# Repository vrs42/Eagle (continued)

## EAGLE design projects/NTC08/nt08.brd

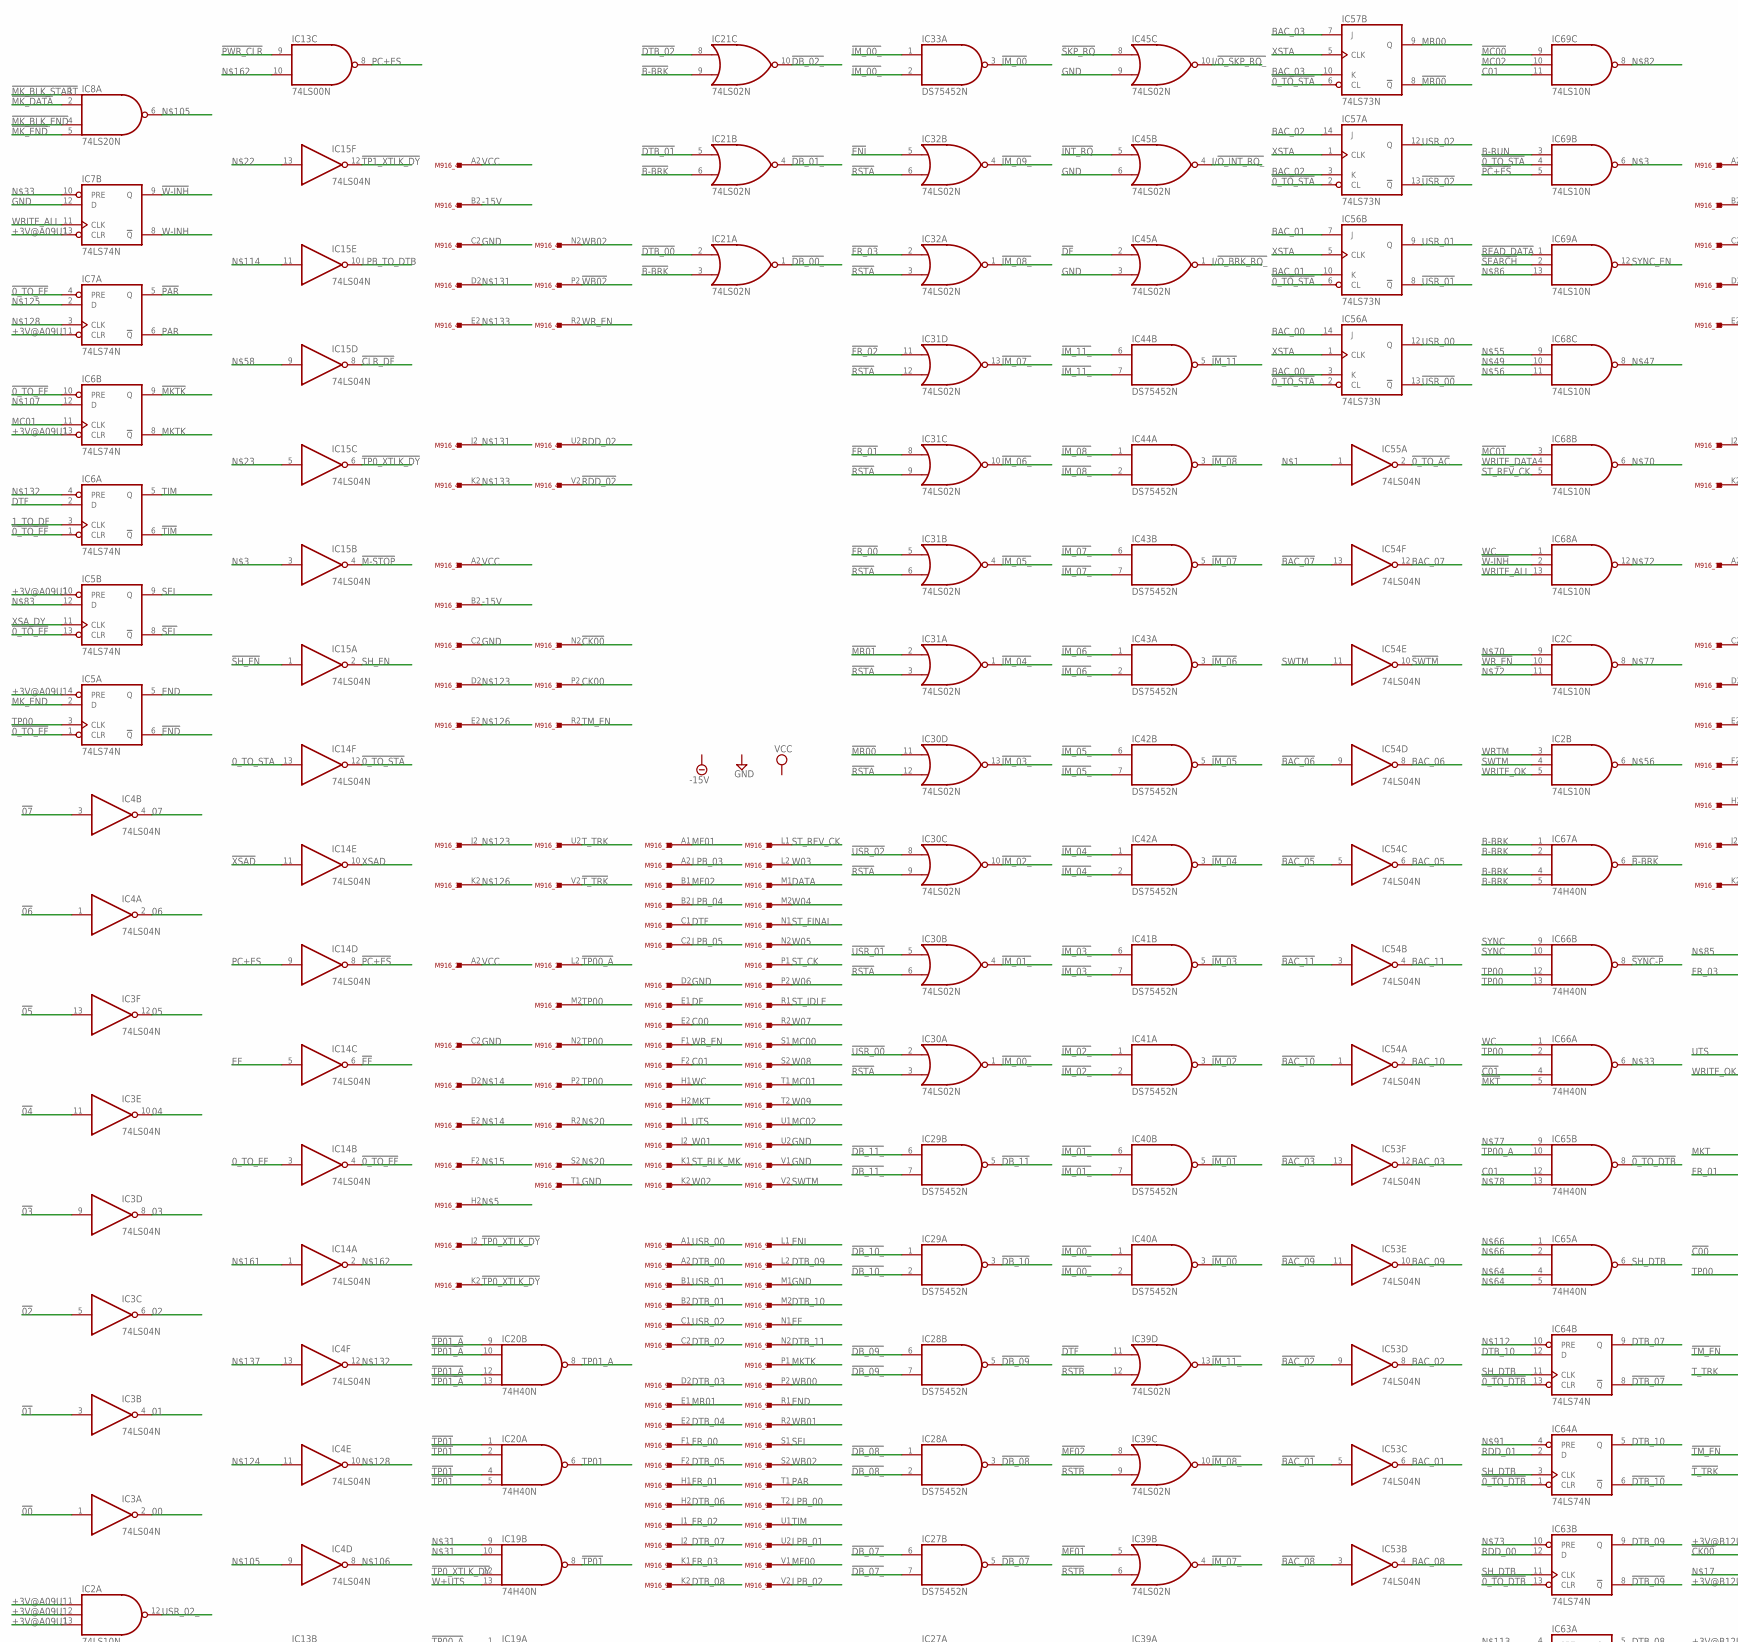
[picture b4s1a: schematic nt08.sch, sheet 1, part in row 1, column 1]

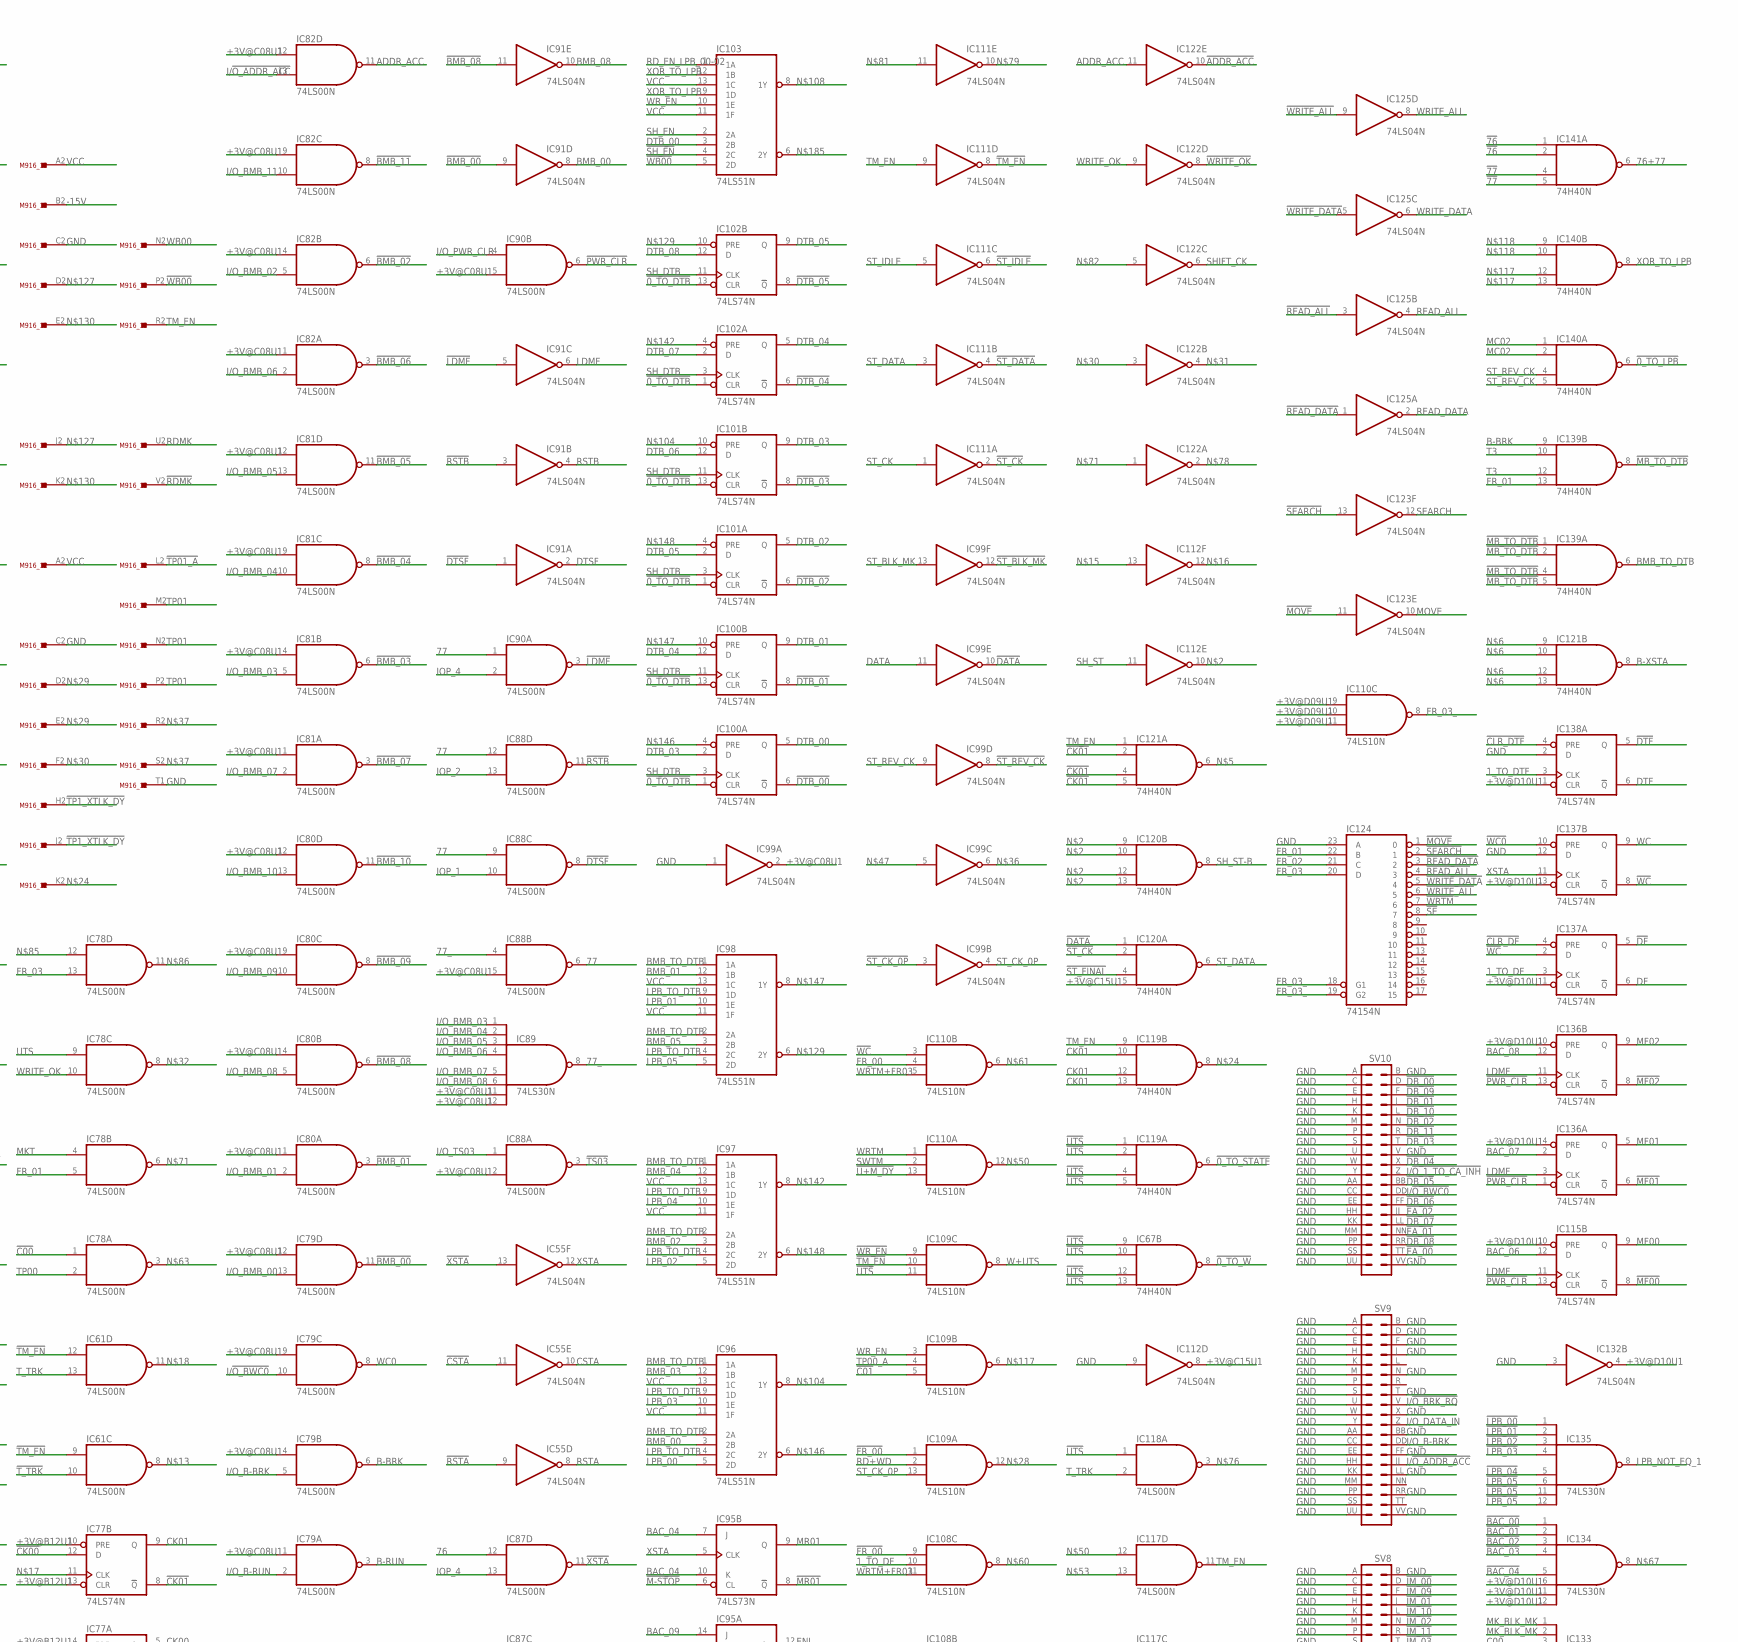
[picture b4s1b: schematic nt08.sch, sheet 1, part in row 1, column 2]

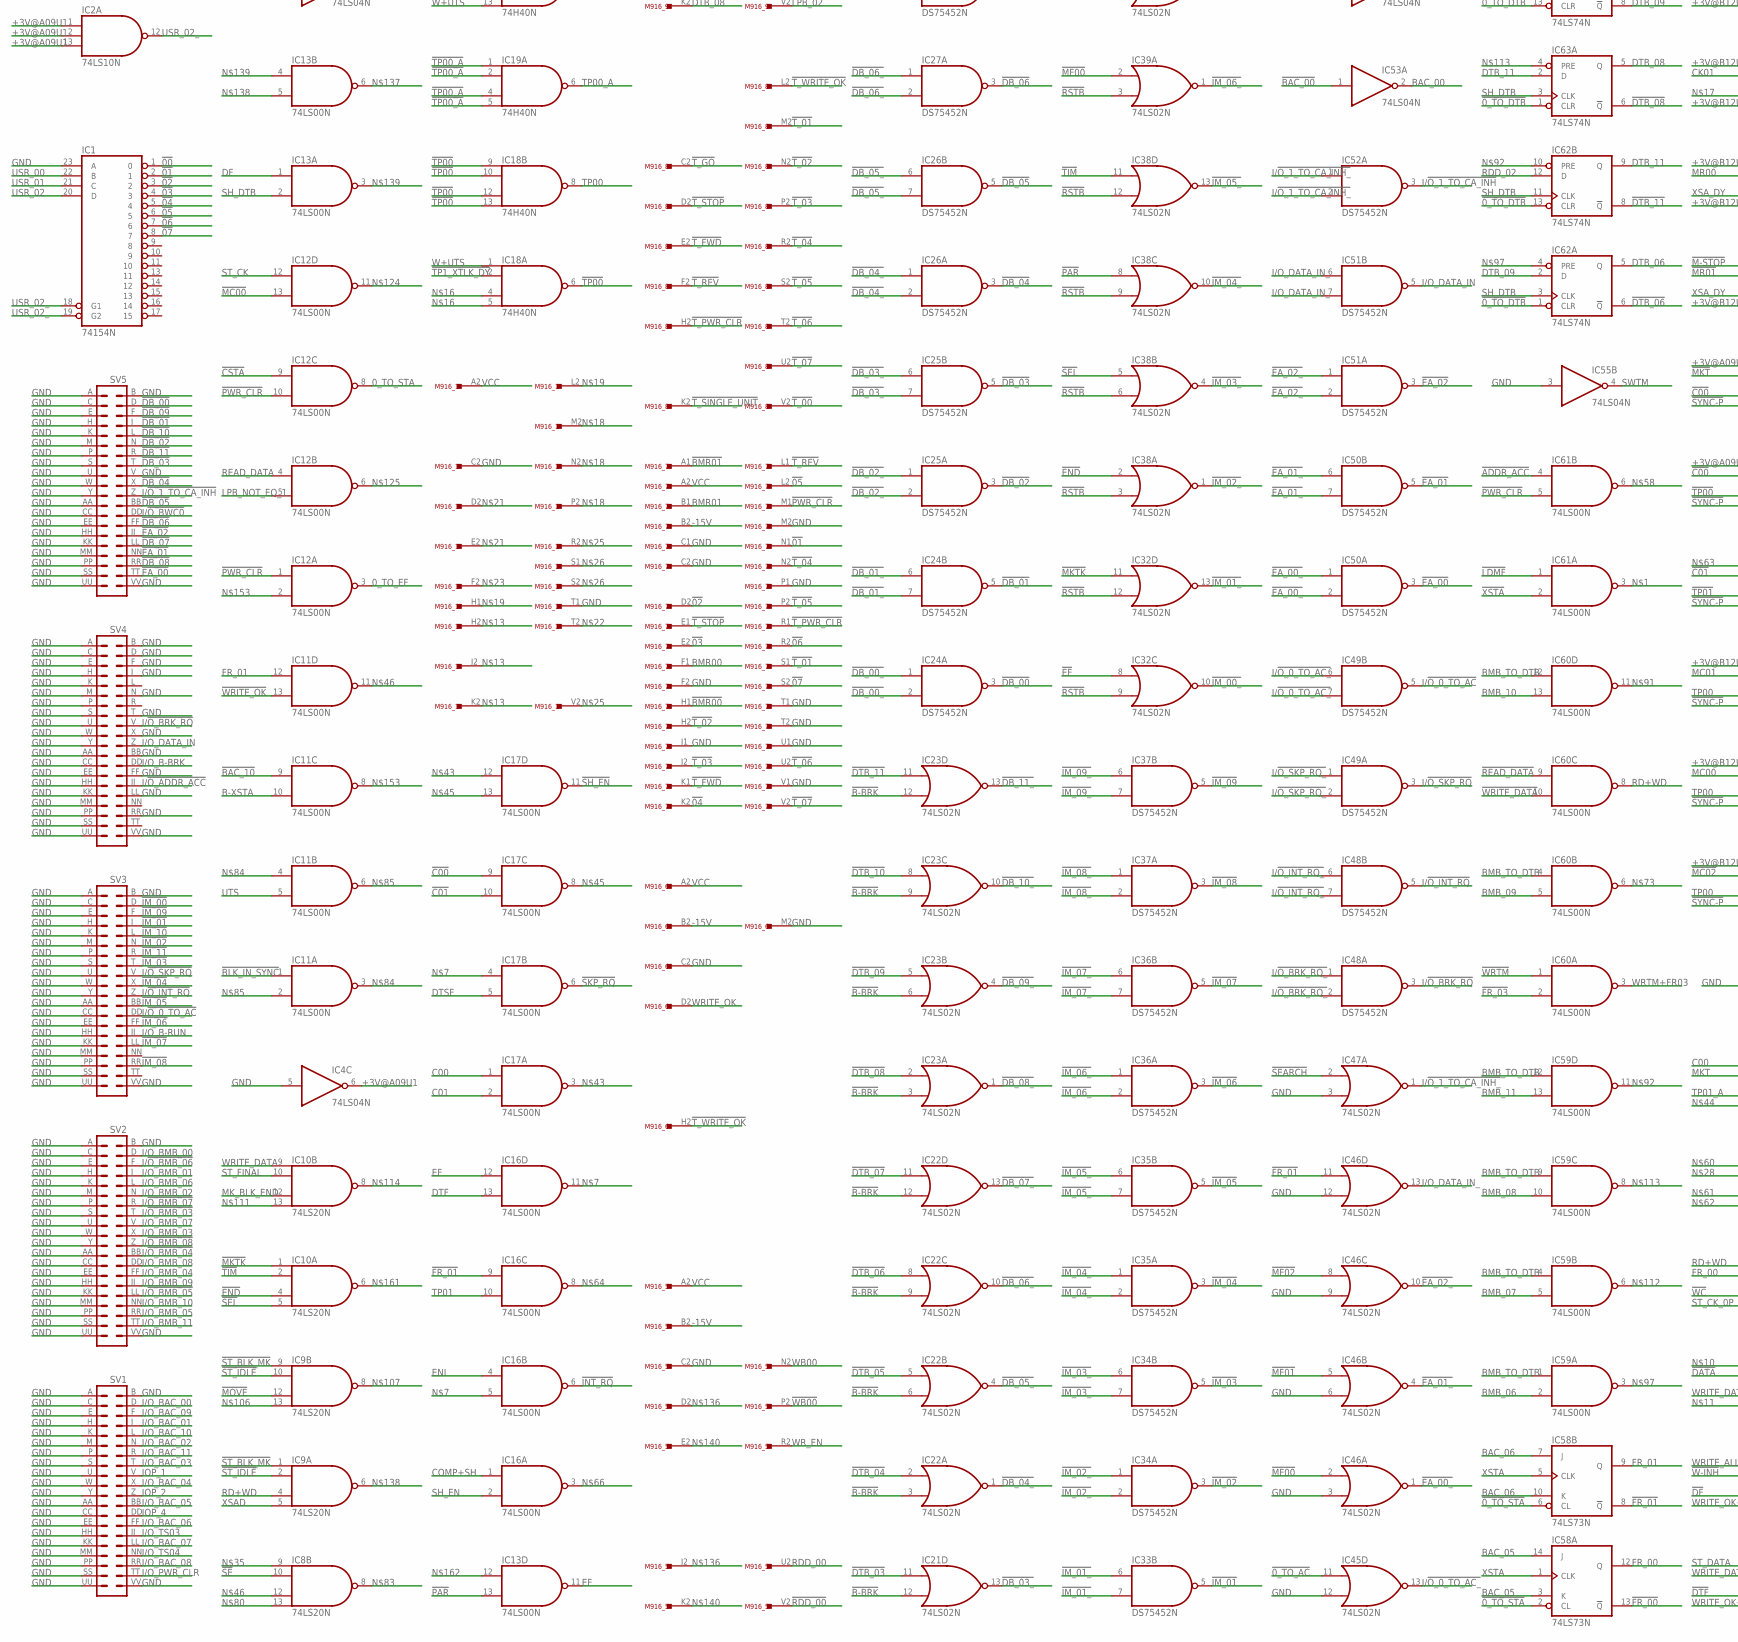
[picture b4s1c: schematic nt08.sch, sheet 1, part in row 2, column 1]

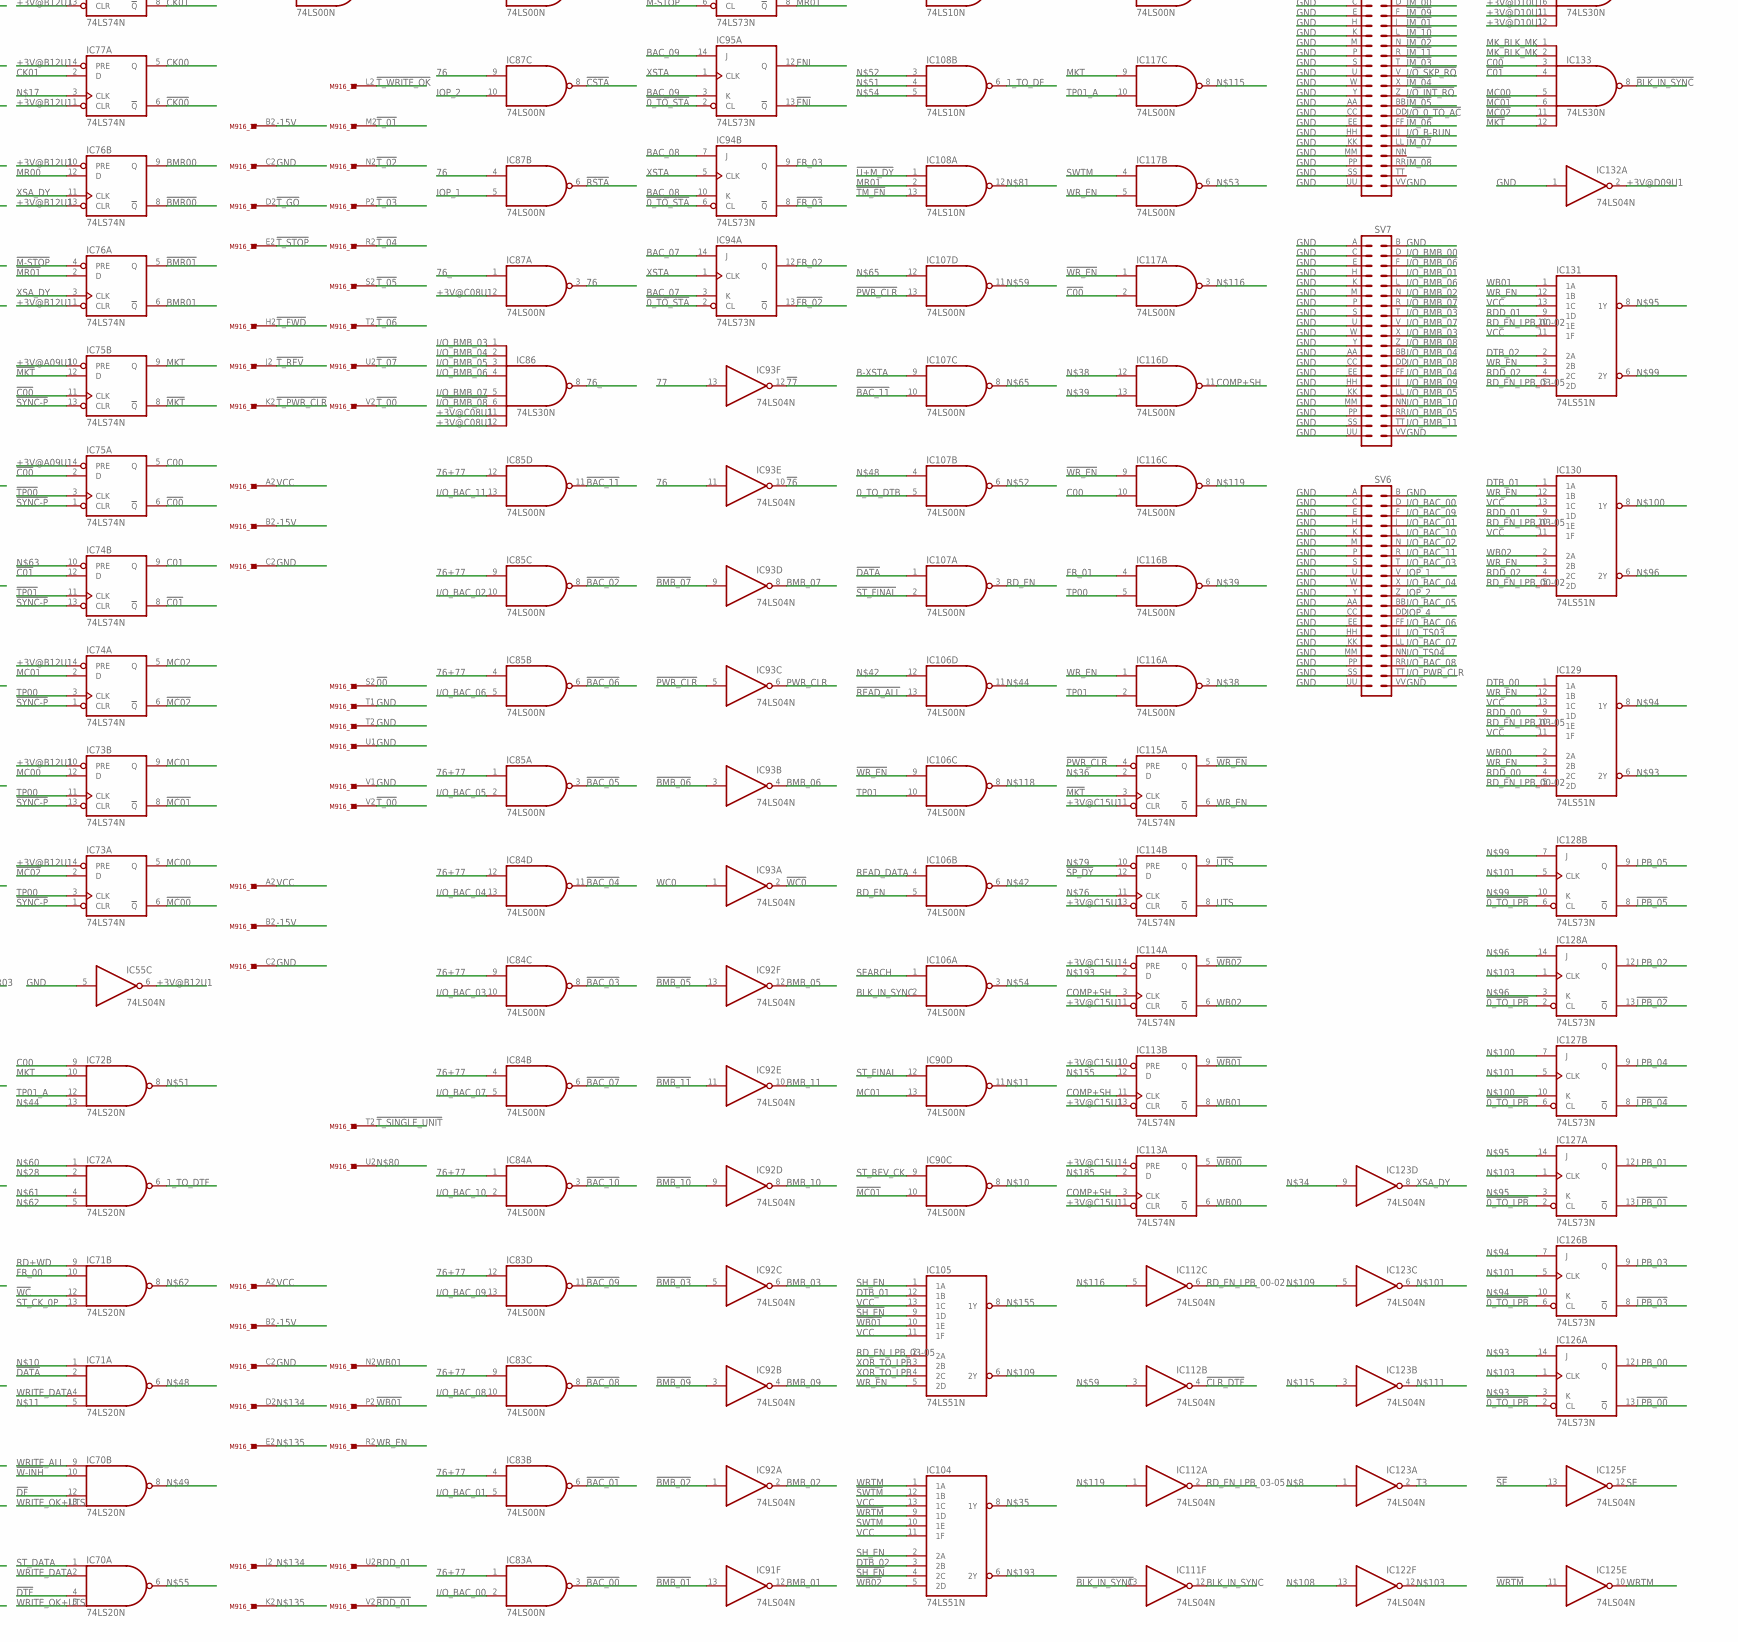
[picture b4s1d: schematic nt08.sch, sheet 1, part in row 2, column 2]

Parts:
IC1, IC124: 74154N; DIL24-6
IC2, IC68, IC69, IC108, IC109, IC110: 74LS10N; DIL14
IC3, IC4, IC14, IC15, IC53, IC54, IC55, IC91, IC92, IC93, IC99, IC111, IC112, IC122, IC123, IC125, IC132: 74LS04N; DIL14
IC5, IC6, IC7, IC62, IC63, IC64, IC73, IC74, IC75, IC76, IC77, IC100, IC101, IC102, IC113, IC114, IC115, IC136, IC137, IC138: 74LS74N; DIL14
IC8, IC9, IC10, IC70, IC71, IC72: 74LS20N; DIL14
IC11, IC12, IC13, IC16, IC17, IC59, IC60, IC61, IC78, IC79, IC80, IC81, IC82, IC83, IC84, IC85, IC87, IC88, IC90, IC106, IC107, IC116, IC117, IC118: 74LS00N; DIL14
IC18, IC19, IC20, IC65, IC66, IC67, IC119, IC120, IC121, IC139, IC140, IC141: 74H40N; DIL14
IC21, IC22, IC23, IC30, IC31, IC32, IC38, IC39, IC45, IC46, IC47: 74LS02N; DIL14
IC24, IC25, IC26, IC27, IC28, IC29, IC33, IC34, IC35, IC36, IC37, IC40, IC41, IC42, IC43, IC44, IC48, IC49, IC50, IC51, IC52: DS75452N; DIL08
IC56, IC57, IC58, IC94, IC95, IC126, IC127, IC128: 74LS73N; DIL14
IC86, IC89, IC133, IC134, IC135: 74LS30N; DIL14
IC96, IC97, IC98, IC103, IC104, IC105, IC129, IC130, IC131: 74LS51N; DIL14
M916_1, M916_4: M302; H807
M916_2, M916_12: M602; H807
M916_3, M916_5, M916_6, M916_13, M916_14: G888; H807
M916_7, M916_16: M633; H807
M916_8: W023; H807
M916_9, M916_10: M916; H807
M916_15: G879; H807
M916_17: W005; H807
SV1, SV2, SV3, SV4, SV5, SV6, SV7, SV8, SV9, SV10: DEC40PINV

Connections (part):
00: IC3.2 (O)
0_TO_DTB: IC107.5 (I1)
0_TO_EF: IC12.3 (O), IC14.3 (I)
0_TO_STA: IC12.8 (O), IC14.13 (I)
01: IC3.4 (O)
1_TO_DF: IC6.3 (CLK), IC108.6 (O), IC108.10 (I1), IC137.3 (CLK)
1_TO_DTF: IC72.6 (O), IC138.3 (CLK)
02: IC3.6 (O)
03: IC3.8 (O)
04: IC3.10 (O)
05: IC3.12 (O)
06: IC4.2 (O)
07: IC4.4 (O)
76: IC87.3 (O), IC87.4 (I0), IC87.9 (I0), IC87.12 (I0), IC93.11 (I)
76+77: IC83.1 (I0), IC83.4 (I0), IC83.9 (I0), IC83.12 (I0), IC84.1 (I0), IC84.4 (I0), IC84.9 (I0), IC84.12 (I0), IC85.1 (I0), IC85.4 (I0), IC85.9 (I0), IC85.12 (I0), IC141.6 (O)
76_: IC86.8 (O), IC87.1 (I0)
77: IC88.6 (O), IC88.9 (I0), IC88.12 (I0), IC90.1 (I0), IC93.13 (I)
77_: IC88.4 (I0), IC89.8 (O)
!00: IC1.1 (0), IC3.1 (I), M916_16.S2
!0_TO_AC: IC45.11 (I0), IC55.2 (O)
!0_TO_DTB: IC62.1 (CLR), IC62.13 (CLR), IC63.1 (CLR), IC63.13 (CLR), IC64.1 (CLR), IC64.13 (CLR), IC65.8 (O), IC100.1 (CLR), IC100.13 (CLR), IC101.1 (CLR), IC101.13 (CLR), IC102.1 (CLR), IC102.13 (CLR)
!0_TO_EF: IC5.1 (CLR), IC5.13 (CLR), IC6.1 (CLR), IC6.10 (PRE), IC7.4 (PRE), IC14.4 (O)
!0_TO_LPB: IC126.2 (CL), IC126.6 (CL), IC127.2 (CL), IC127.6 (CL), IC128.2 (CL), IC128.6 (CL), IC140.6 (O)
!0_TO_STA: IC14.12 (O), IC56.2 (CL), IC56.6 (CL), IC57.2 (CL), IC57.6 (CL), IC58.2 (CL), IC58.6 (CL), IC69.4 (I1), IC94.2 (CL), IC94.6 (CL), IC95.2 (CL)
!0_TO_STATE: IC119.6 (O)
!0_TO_W: IC67.8 (O)
!01: IC1.2 (1), IC3.3 (I), M916_7.N1
!02: IC1.3 (2), IC3.5 (I), M916_7.D2
!03: IC1.4 (3), IC3.9 (I), M916_7.E2
!04: IC1.5 (4), IC3.11 (I), M916_7.K2
!05: IC1.6 (5), IC3.13 (I), M916_7.L2
!06: IC1.7 (6), IC4.1 (I), M916_7.R2
!07: IC1.8 (7), IC4.3 (I), M916_7.S2
!76: IC93.10 (O), IC141.1 (I0), IC141.2 (I1)
!77: IC93.12 (O), IC141.4 (I2), IC141.5 (I3)
!ADDR_ACC: IC61.4 (I0), IC122.10 (O)
!B-BRK: IC21.3 (I1), IC21.6 (I1), IC21.9 (I1), IC21.12 (I1), IC22.3 (I1), IC22.6 (I1), IC22.9 (I1), IC22.12 (I1), IC23.3 (I1), IC23.6 (I1), IC23.9 (I1), IC23.12 (I1), IC67.6 (O)
!BAC_00: IC53.1 (I), IC83.3 (O), IC134.1 (I0)
!BAC_01: IC53.5 (I), IC83.6 (O), IC134.2 (I1)
!BAC_02: IC53.9 (I), IC85.8 (O), IC134.3 (I2)
!BAC_03: IC53.13 (I), IC84.8 (O), IC134.4 (I3)
!BAC_04: IC84.11 (O), IC134.5 (I4)
!BAC_05: IC54.5 (I), IC85.3 (O)
!BAC_06: IC54.9 (I), IC85.6 (O)
!BAC_07: IC54.13 (I), IC84.6 (O)
!BAC_08: IC53.3 (I), IC83.8 (O)
!BAC_09: IC53.11 (I), IC83.11 (O)
!BAC_10: IC11.9 (I0), IC54.1 (I), IC84.3 (O)
!BAC_11: IC54.3 (I), IC85.11 (O), IC107.10 (I1)
!BLK_IN_SYNC: IC11.1 (I0), IC111.13 (I), IC133.8 (O)
!BMB_00: IC79.11 (O), IC91.9 (I)
!BMB_01: IC80.3 (O), IC91.13 (I)
!BMB_02: IC82.6 (O), IC92.1 (I)
!BMB_03: IC81.6 (O), IC92.5 (I)
!BMB_04: IC81.8 (O)
!BMB_05: IC81.11 (O), IC92.13 (I)
!BMB_06: IC82.3 (O), IC93.3 (I)
!BMB_07: IC81.3 (O), IC93.9 (I)
!BMB_08: IC80.6 (O), IC91.11 (I)
!BMB_09: IC80.8 (O), IC92.3 (I)
!BMB_10: IC80.11 (O), IC92.9 (I)
!BMB_11: IC82.8 (O), IC92.11 (I)
!BMR00: IC76.8 (!Q), M916_7.H1
!BMR01: IC76.5 (Q), M916_7.A1
!C00: IC17.9 (I0), IC75.2 (D), IC75.6 (!Q), IC75.11 (CLK), IC78.1 (I0), IC117.2 (I1)
!C01: IC17.10 (I1), IC66.4 (I2), IC74.8 (!Q), IC74.12 (D), IC109.5 (I2), IC133.4 (I3)
!CK00: IC77.6 (!Q), IC77.12 (D), M916_3.N2
!CK01: IC77.8 (!Q), IC121.2 (I1), IC121.4 (I2), IC121.5 (I3)
!CLR_DF: IC15.8 (O), IC137.4 (PRE)
!CLR_DTF: IC112.4 (O), IC138.4 (PRE)
!CSTA: IC12.9 (I0), IC55.11 (I), IC87.8 (O)
!DATA: IC71.2 (I1), IC99.10 (O), IC107.1 (I0), IC120.1 (I0)
!DB_00: IC24.3 (O), SV5.D (4), SV10.D (4)
!DB_00_: IC21.1 (O), IC24.1 (I0), IC24.2 (I1)
!DB_01: IC24.5 (O), SV5.J (8), SV10.J (8)
!DB_01_: IC21.4 (O), IC24.6 (I0), IC24.7 (I1)
!DB_02: IC25.3 (O), SV5.N (12), SV10.N (12)
!DB_02_: IC21.10 (O), IC25.1 (I0), IC25.2 (I1)
!DB_03: IC25.5 (O), SV5.T (16), SV10.T (16)
!DB_03_: IC21.13 (O), IC25.6 (I0), IC25.7 (I1)
!DB_04: IC26.3 (O), SV5.X (20), SV10.X (20)
!DB_04_: IC22.1 (O), IC26.1 (I0), IC26.2 (I1)
!DB_05: IC26.5 (O), SV5.BB (24), SV10.BB (24)
!DB_05_: IC22.4 (O), IC26.6 (I0), IC26.7 (I1)
!DB_06: IC27.3 (O), SV5.FF (28), SV10.FF (28)
!DB_06_: IC22.10 (O), IC27.1 (I0), IC27.2 (I1)
!DB_07: IC27.5 (O), SV5.LL (32), SV10.LL (32)
!DB_07_: IC22.13 (O), IC27.6 (I0), IC27.7 (I1)
!DB_08: IC28.3 (O), SV5.RR (36), SV10.RR (36)
!DB_08_: IC23.1 (O), IC28.1 (I0), IC28.2 (I1)
!DB_09: IC28.5 (O), SV5.F (6), SV10.F (6)
!DB_09_: IC23.4 (O), IC28.6 (I0), IC28.7 (I1)
!DB_10: IC29.3 (O), SV5.L (10), SV10.L (10)
!DB_10_: IC23.10 (O), IC29.1 (I0), IC29.2 (I1)
!DB_11: IC29.5 (O), SV5.R (14), SV10.R (14)
!DB_11_: IC23.13 (O), IC29.6 (I0), IC29.7 (I1)
!DF: IC45.2 (I0), IC70.12 (I2), IC137.5 (Q)
!DTB_00: IC21.2 (I0), IC100.6 (!Q)
!DTB_01: IC21.5 (I0), IC100.8 (!Q)
!DTB_02: IC21.8 (I0), IC101.6 (!Q)
!DTB_03: IC21.11 (I0), IC101.8 (!Q)
!DTB_04: IC22.2 (I0), IC102.6 (!Q)
!DTB_05: IC22.5 (I0), IC102.8 (!Q)
!DTB_06: IC22.8 (I0), IC62.6 (!Q)
!DTB_07: IC22.11 (I0), IC64.8 (!Q)
!DTB_08: IC23.2 (I0), IC63.6 (!Q)
!DTB_09: IC23.5 (I0), IC63.8 (!Q)
!DTB_10: IC23.8 (I0), IC64.6 (!Q)
!DTB_11: IC23.11 (I0), IC62.8 (!Q)
!DTF: IC39.11 (I0), IC70.4 (I2), IC138.5 (Q)
!DTSF: IC88.8 (O), IC91.1 (I)
!EA_00: IC50.3 (O), SV5.TT (38), SV10.TT (38)
!EA_00_: IC46.1 (O), IC50.1 (I0), IC50.2 (I1)
!EA_01: IC50.5 (O), SV5.NN (34), SV10.NN (34)
!EA_01_: IC46.4 (O), IC50.6 (I0), IC50.7 (I1)
!EA_02: IC51.3 (O), SV5.JJ (30), SV10.JJ (30)
!EA_02_: IC46.10 (O), IC51.1 (I0), IC51.2 (I1)
!EF: IC14.6 (O), IC32.8 (I0)
!END: IC5.6 (!Q), IC10.4 (I2), IC38.2 (I0)
!ENI: IC32.5 (I0), IC95.13 (!Q)
!FR_00: IC31.5 (I0), IC58.13 (!Q), IC108.9 (I0), IC109.1 (I0)
!FR_01: IC16.9 (I0), IC31.8 (I0), IC46.11 (I0), IC58.8 (!Q)
!FR_02: IC31.11 (I0), IC94.13 (!Q)
!FR_03: IC32.2 (I0), IC60.2 (I1), IC94.8 (!Q)
!IM_00: IC33.3 (O), IC40.3 (O), SV3.D (4), SV8.D (4)
!IM_00_: IC30.1 (O), IC32.10 (O), IC33.1 (I0), IC33.2 (I1), IC40.1 (I0), IC40.2 (I1)
!IM_01: IC33.5 (O), IC40.5 (O), SV3.J (8), SV8.J (8)
!IM_01_: IC30.4 (O), IC32.13 (O), IC33.6 (I0), IC33.7 (I1), IC40.6 (I0), IC40.7 (I1)
!IM_02: IC34.3 (O), IC41.3 (O), SV3.N (12), SV8.N (12)
!IM_02_: IC30.10 (O), IC34.1 (I0), IC34.2 (I1), IC38.1 (O), IC41.1 (I0), IC41.2 (I1)
!IM_03: IC34.5 (O), IC41.5 (O), SV3.T (16), SV8.T (16)
!IM_03_: IC30.13 (O), IC34.6 (I0), IC34.7 (I1), IC38.4 (O), IC41.6 (I0), IC41.7 (I1)
!IM_04: IC35.3 (O), IC42.3 (O), SV3.X (20), SV8.X (20)
!IM_04_: IC31.1 (O), IC35.1 (I0), IC35.2 (I1), IC38.10 (O), IC42.1 (I0), IC42.2 (I1)
!IM_05: IC35.5 (O), IC42.5 (O), SV3.BB (24), SV8.BB (24)
!IM_05_: IC31.4 (O), IC35.6 (I0), IC35.7 (I1), IC38.13 (O), IC42.6 (I0), IC42.7 (I1)
!IM_06: IC36.3 (O), IC43.3 (O), SV3.FF (28), SV8.FF (28)
!IM_06_: IC31.10 (O), IC36.1 (I0), IC36.2 (I1), IC39.1 (O), IC43.1 (I0), IC43.2 (I1)
!IM_07: IC36.5 (O), IC43.5 (O), SV3.LL (32), SV8.LL (32)
!IM_07_: IC31.13 (O), IC36.6 (I0), IC36.7 (I1), IC39.4 (O), IC43.6 (I0), IC43.7 (I1)
!IM_08: IC37.3 (O), IC44.3 (O), SV3.RR (36), SV8.RR (36)
!IM_08_: IC32.1 (O), IC37.1 (I0), IC37.2 (I1), IC39.10 (O), IC44.1 (I0), IC44.2 (I1)
!IM_09: IC37.5 (O), SV3.F (6), SV8.F (6)
!IM_09_: IC32.4 (O), IC37.6 (I0), IC37.7 (I1)
!IM_10: SV3.L (10), SV8.L (10)
!IM_11: IC44.5 (O), SV3.R (14), SV8.R (14)
!IM_11_: IC39.13 (O), IC44.6 (I0), IC44.7 (I1)
!INT_RQ: IC16.6 (O), IC45.5 (I0)
!LDMF: IC61.1 (I0), IC90.3 (O), IC91.5 (I)
!LPB_00: IC126.13 (!Q), IC135.1 (I0)
!LPB_01: IC127.13 (!Q), IC135.2 (I1)
!LPB_02: IC128.13 (!Q), IC135.3 (I2)
!LPB_03: IC126.8 (!Q), IC135.4 (I3)
!LPB_04: IC127.8 (!Q), IC135.5 (I4)
!LPB_05: IC128.8 (!Q), IC135.6 (I5), IC135.11 (I6), IC135.12 (I7)
!M-STOP: IC15.4 (O), IC76.4 (PRE), IC95.6 (CL); also elsewhere on the board
!MB_TO_DTB: IC139.1 (I0), IC139.2 (I1), IC139.4 (I2), IC139.5 (I3), IC139.8 (O)
!MC00: IC12.13 (I1), IC69.9 (I0), IC73.6 (!Q)
!MC01: IC68.3 (I0), IC73.8 (!Q), IC90.10 (I1), IC133.6 (I5)
!MC02: IC73.2 (D), IC74.6 (!Q), IC133.11 (I6)
!MF00: IC39.2 (I0), IC46.2 (I0), IC115.8 (!Q)
!MF01: IC39.5 (I0), IC46.5 (I0), IC136.6 (!Q)
!MF02: IC39.8 (I0), IC46.8 (I0), IC136.8 (!Q)
!MKT: IC66.5 (I3), IC75.8 (!Q), IC75.12 (D), IC115.3 (CLK), IC133.12 (I7)
!MKTK: IC6.9 (Q), IC10.1 (I0), IC32.11 (I0)
!MK_BLK_END: IC8.4 (I2)
!MK_BLK_START: IC8.1 (I0)
!MK_DATA: IC8.2 (I1)
!MK_END: IC8.5 (I3)
!MOVE: IC9.12 (I2), IC123.11 (I), IC124.1 (0)
!MR00: IC30.11 (I0), IC57.8 (!Q)
!MR01: IC31.2 (I0), IC76.2 (D), IC95.8 (!Q)
!PAR: IC7.5 (Q), IC13.13 (I1), IC38.8 (I0)
!PC+ES: IC14.8 (O), IC69.5 (I2)
!PWR_CLR: IC12.1 (I0), IC12.10 (I1), IC13.9 (I0), IC61.5 (I1), IC90.6 (O), IC93.5 (I), IC107.13 (I1), IC115.4 (PRE), IC115.13 (CLR), IC136.1 (CLR), IC136.13 (CLR), M916_7.M1
!RDD_00: M916_5.V2
!RDD_01: M916_14.V2
!RDD_02: M916_4.V2
!RDMK: M916_13.V2
!READ_ALL: IC106.13 (I1), IC124.4 (3), IC125.3 (I)
!READ_DATA: IC60.9 (I0), IC69.1 (I0), IC124.3 (2), IC125.1 (I)
!RSTA: IC30.3 (I1), IC30.6 (I1), IC30.9 (I1), IC30.12 (I1), IC31.3 (I1), IC31.6 (I1), IC31.9 (I1), IC31.12 (I1), IC32.3 (I1), IC32.6 (I1), IC55.9 (I), IC87.6 (O)
!RSTB: IC32.9 (I1), IC32.12 (I1), IC38.3 (I1), IC38.6 (I1), IC38.9 (I1), IC38.12 (I1), IC39.3 (I1), IC39.6 (I1), IC39.9 (I1), IC39.12 (I1), IC88.11 (O), IC91.3 (I)
!SE: IC8.10 (I1), IC124.8 (7), IC125.13 (I)
!SEARCH: IC47.2 (I0), IC69.2 (I1), IC123.13 (I), IC124.2 (1)
!SEL: IC5.8 (!Q), IC10.5 (I3), IC38.5 (I0)
!SH_EN: IC15.1 (I), IC17.11 (O), IC103.4 (2C), IC104.4 (2C), IC105.9 (1D)
!SKP_RQ: IC17.6 (O), IC45.8 (I0)
!SP_DY: IC114.12 (D); also elsewhere on the board
!ST_BLK_MK: IC9.1 (I0), IC9.9 (I0), IC99.12 (O)
!ST_CK: IC111.2 (O), IC120.2 (I1)
!ST_CK_0P: IC99.3 (I); also elsewhere on the board
!ST_DATA: IC111.4 (O)
!ST_FINAL: IC107.2 (I1), IC120.4 (I2)
!ST_IDLE: IC9.2 (I1), IC9.10 (I1), IC111.6 (O)
!ST_REV_CK: IC99.8 (O)
!SWTM: IC54.10 (O), IC104.12 (1B)
!SYNC-P: IC66.8 (O), IC73.1 (CLR), IC73.13 (CLR), IC74.1 (CLR), IC74.13 (CLR), IC75.1 (CLR), IC75.13 (CLR)
!TIM: IC6.6 (!Q), IC10.2 (I1), IC38.11 (I0)
!TM_EN: IC61.9 (I0), IC61.12 (I0), IC108.13 (I2), IC109.10 (I1), IC111.8 (O); also elsewhere on the board
!TP00: IC18.6 (O), IC18.9 (I0), IC18.10 (I1), IC18.12 (I2), IC18.13 (I3), IC75.3 (CLK)
!TP00_A: IC19.1 (I0), IC19.2 (I1), IC19.4 (I2), IC19.5 (I3), M916_2.L2
!TP0_XTLK_DY: IC15.6 (O), IC19.12 (I2), M916_2.J2, M916_2.K2
!TP01: IC19.8 (O), IC20.1 (I0), IC20.2 (I1), IC20.4 (I2), IC20.5 (I3), IC74.11 (CLK)
!TP01_A: IC20.9 (I0), IC20.10 (I1), IC20.12 (I2), IC20.13 (I3), M916_12.L2
!TP1_XTLK_DY: IC15.12 (O), IC18.2 (I1), M916_12.H2, M916_12.J2
!TS03: IC88.3 (O); also elsewhere on the board
!T_00: M916_8.V2, M916_16.V2, M916_17.V2
!T_01: M916_7.S1, M916_8.M2, M916_17.M2
!T_02: M916_7.H2, M916_8.N2, M916_17.N2
!T_03: M916_7.J2, M916_8.P2, M916_17.P2
!T_04: M916_7.N2, M916_8.R2, M916_17.R2
!T_05: M916_7.P2, M916_8.S2, M916_17.S2
!T_06: M916_7.U2, M916_8.T2, M916_17.T2
!T_07: M916_7.V2, M916_8.U2, M916_17.U2
!T_FWD: M916_7.K1, M916_8.E2, M916_17.H2
!T_GO: M916_8.C2, M916_17.D2
!T_PWR_CLR: M916_7.R1, M916_8.H2, M916_17.K2
!T_REV: M916_7.L1, M916_8.F2, M916_17.J2
!T_SINGLE_UNIT: M916_8.K2, M916_15.T2
!T_STOP: M916_7.E1, M916_8.D2, M916_17.E2
!T_TRK: IC61.10 (I1), M916_3.V2
!T_WRITE_OK: M916_6.H2, M916_8.L2, M916_17.L2
!U+M_DY: IC108.1 (I0), IC110.13 (I2); also elsewhere on the board
!USR_00: IC30.2 (I0), IC56.13 (!Q)
!USR_01: IC30.5 (I0), IC56.8 (!Q)
!USR_02: IC30.8 (I0), IC57.13 (!Q)
!UTS: IC67.9 (I0), IC67.10 (I1), IC67.12 (I2), IC67.13 (I3), IC109.11 (I2), IC114.9 (Q), IC118.1 (I0), IC119.1 (I0), IC119.2 (I1), IC119.4 (I2), IC119.5 (I3)
!W-INH: IC7.9 (Q), IC68.2 (I1), IC70.10 (I1)
!WB00: IC103.5 (2D), IC113.5 (Q), M916_5.P2, M916_13.P2
!WB01: IC105.10 (1E), IC113.9 (Q), M916_14.P2
!WB02: IC104.5 (2D), IC114.5 (Q), M916_4.P2
!WC: IC71.12 (I2), IC110.3 (I0), IC137.2 (D), IC137.8 (!Q)
!WC0: IC93.2 (O), IC137.10 (PRE)
!WRITE_ALL: IC124.6 (5), IC125.9 (I)
!WRITE_DATA: IC60.10 (I1), IC124.5 (4), IC125.5 (I)
!WRITE_OK: IC11.13 (I1), IC122.8 (O)
!WRTM: IC60.1 (I0), IC104.9 (1D), IC124.7 (6), IC125.11 (I)
!WR_EN: IC2.10 (I1), IC106.9 (I0), IC109.9 (I0), IC115.5 (Q), IC116.9 (I0), IC117.1 (I0)
!XSAD: IC14.11 (I); also elsewhere on the board
!XSTA: IC55.13 (I), IC61.2 (I1), IC87.11 (O); also elsewhere on the board
+3V@A09U1: IC2.1 (I0), IC2.2 (I1), IC2.13 (I2), IC4.6 (O), IC5.4 (PRE), IC5.10 (PRE), IC6.13 (CLR), IC7.1 (CLR), IC7.13 (CLR), IC75.4 (PRE), IC75.10 (PRE)
+3V@B12U1: IC55.6 (O), IC73.4 (PRE), IC73.10 (PRE), IC74.4 (PRE), IC76.1 (CLR), IC76.10 (PRE), IC76.13 (CLR), IC77.1 (CLR), IC77.4 (PRE), IC77.10 (PRE), IC77.13 (CLR)
+3V@C08U1: IC79.1 (I0), IC79.4 (I0), IC79.9 (I0), IC79.12 (I0), IC80.1 (I0), IC80.4 (I0), IC80.9 (I0), IC80.12 (I0), IC81.1 (I0), IC81.4 (I0), IC81.9 (I0), IC81.12 (I0), IC82.1 (I0), IC82.4 (I0), IC82.9 (I0), IC82.12 (I0), IC86.11 (I6), IC86.12 (I7), IC87.2 (I1), IC88.2 (I1), IC88.5 (I1), IC89.11 (I6), IC89.12 (I7), IC90.5 (I1), IC99.2 (O)
+3V@C15U1: IC112.8 (O), IC113.1 (CLR), IC113.4 (PRE), IC113.10 (PRE), IC113.13 (CLR), IC114.1 (CLR), IC114.4 (PRE), IC114.13 (CLR), IC115.1 (CLR), IC120.5 (I3)
+3V@D09U1: IC110.9 (I0), IC110.10 (I1), IC110.11 (I2), IC132.2 (O)
+3V@D10U1: IC115.10 (PRE), IC132.4 (O), IC134.6 (I5), IC134.11 (I6), IC134.12 (I7), IC136.4 (PRE), IC136.10 (PRE), IC137.1 (CLR), IC137.13 (CLR), IC138.1 (CLR); also elsewhere on the board
-15V: M916_3.B2, M916_4.B2, M916_5.B2, M916_6.B2, M916_7.B2, M916_13.B2, M916_14.B2, M916_15.B2, M916_16.B2, M916_17.B2
ADDR_ACC: IC82.11 (O), IC122.11 (I)
B-BRK: IC67.1 (I0), IC67.2 (I1), IC67.4 (I2), IC67.5 (I3), IC79.6 (O), IC139.9 (I0)
B-RUN: IC69.3 (I0), IC79.3 (O)
B-XSTA: IC11.10 (I1), IC107.9 (I0), IC121.8 (O)
BAC_00: IC53.2 (O), IC56.3 (K), IC56.14 (J)
BAC_01: IC53.6 (O), IC56.7 (J), IC56.10 (K)
BAC_02: IC53.8 (O), IC57.3 (K), IC57.14 (J)
BAC_03: IC53.12 (O), IC57.7 (J), IC57.10 (K)
BAC_04: IC95.7 (J), IC95.10 (K)
BAC_05: IC54.6 (O), IC58.3 (K), IC58.14 (J)
BAC_06: IC54.8 (O), IC58.7 (J), IC58.10 (K), IC115.12 (D)
BAC_07: IC54.12 (O), IC94.3 (K), IC94.14 (J), IC136.2 (D)
BAC_08: IC53.4 (O), IC94.7 (J), IC94.10 (K), IC136.12 (D)
BAC_09: IC53.10 (O), IC95.3 (K), IC95.14 (J)
BAC_10: IC54.2 (O)
BAC_11: IC54.4 (O)
BLK_IN_SYNC: IC106.2 (I1), IC111.12 (O)
BMB_00: IC91.8 (O), IC96.3 (2B)
BMB_01: IC91.12 (O), IC98.12 (1B)
BMB_02: IC92.2 (O), IC97.3 (2B)
BMB_03: IC92.6 (O), IC96.12 (1B)
BMB_04: IC97.12 (1B)
BMB_05: IC92.12 (O), IC98.3 (2B)
BMB_06: IC59.2 (I1), IC93.4 (O)
BMB_07: IC59.5 (I1), IC93.8 (O)
BMB_08: IC59.10 (I1), IC91.10 (O)
BMB_09: IC60.5 (I1), IC92.4 (O)
BMB_10: IC60.13 (I1), IC92.8 (O)
BMB_11: IC59.13 (I1), IC92.10 (O)
BMB_TO_DTB: IC59.1 (I0), IC59.4 (I0), IC59.9 (I0), IC59.12 (I0), IC60.4 (I0), IC60.12 (I0), IC96.1 (1A), IC96.2 (2A), IC97.1 (1A), IC97.2 (2A), IC98.1 (1A), IC98.2 (2A), IC139.6 (O)
BMR00: IC76.9 (Q), M916_7.F1
BMR01: IC76.6 (!Q), M916_7.B1
C00: IC17.1 (I0), IC72.9 (I0), IC75.5 (Q), IC116.10 (I1), IC133.3 (I2), M916_10.E2
C01: IC17.2 (I1), IC65.12 (I2), IC69.11 (I2), IC74.9 (Q), M916_10.F2
CK00: IC77.5 (Q), M916_3.P2
CK01: IC77.2 (D), IC77.9 (Q), IC119.10 (I1), IC119.12 (I2), IC119.13 (I3)
COMP+SH: IC16.1 (I0), IC113.3 (CLK), IC113.11 (CLK), IC114.3 (CLK), IC116.11 (O)
CSTA: IC55.10 (O); also elsewhere on the board
DATA: IC99.11 (I), M916_10.M1
DF: IC13.1 (I0), IC137.6 (!Q), M916_10.E1
DTB_00: IC100.5 (Q), IC103.3 (2B), IC129.1 (1A), M916_9.A2
DTB_01: IC100.9 (Q), IC105.12 (1B), IC130.1 (1A), M916_9.B2
DTB_02: IC101.5 (Q), IC104.3 (2B), IC131.2 (2A), M916_9.C2
DTB_03: IC100.2 (D), IC101.9 (Q), M916_9.D2
DTB_04: IC100.12 (D), IC102.5 (Q), M916_9.E2
DTB_05: IC101.2 (D), IC102.9 (Q), M916_9.F2
DTB_06: IC62.5 (Q), IC101.12 (D), M916_9.H2
DTB_07: IC64.9 (Q), IC102.2 (D), M916_9.J2
DTB_08: IC63.5 (Q), IC102.12 (D), M916_9.K2
DTB_09: IC62.2 (D), IC63.9 (Q), M916_9.L2
DTB_10: IC64.5 (Q), IC64.12 (D), M916_9.M2
DTB_11: IC62.9 (Q), IC63.2 (D), M916_9.N2
DTF: IC6.2 (D), IC16.13 (I1), IC138.6 (!Q), M916_10.C1
DTSF: IC17.5 (I1), IC91.2 (O)
EF: IC13.11 (O), IC14.5 (I), IC16.12 (I0), M916_9.N1
END: IC5.5 (Q), M916_9.R1
ENI: IC16.4 (I0), IC95.12 (Q), M916_9.L1
FR_00: IC58.12 (Q), IC71.10 (I1), IC110.4 (I1), M916_9.F1
FR_01: IC11.12 (I0), IC58.9 (Q), IC78.5 (I1), IC116.4 (I0), IC124.22 (B), IC139.13 (I3), M916_9.H1
FR_02: IC94.12 (Q), IC124.21 (C), M916_9.J1
FR_03: IC78.13 (I1), IC94.9 (Q), IC124.20 (D), M916_9.K1
FR_03_: IC110.8 (O), IC124.18 (G1), IC124.19 (G2)
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
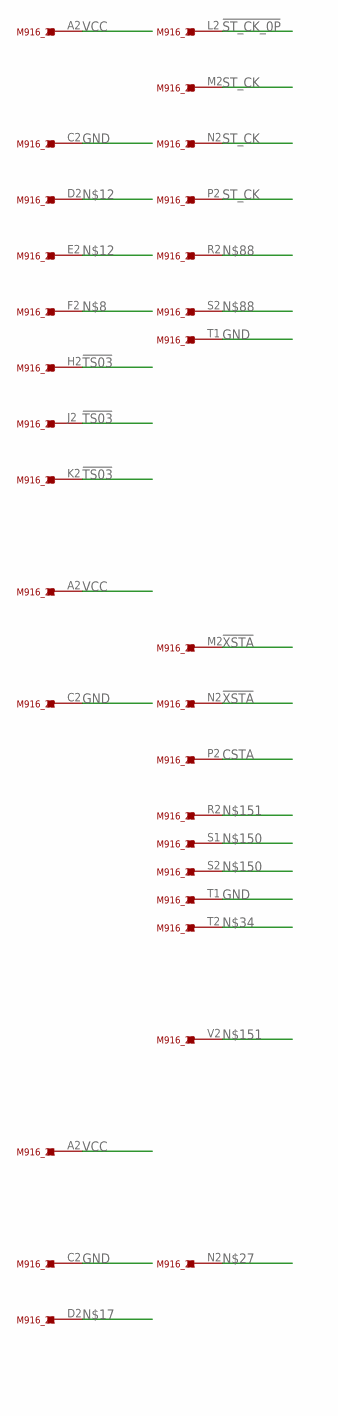
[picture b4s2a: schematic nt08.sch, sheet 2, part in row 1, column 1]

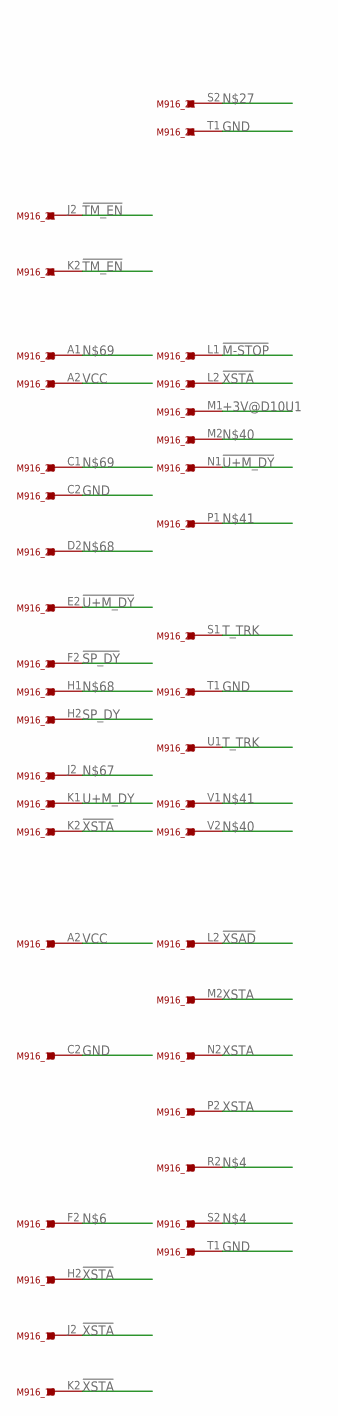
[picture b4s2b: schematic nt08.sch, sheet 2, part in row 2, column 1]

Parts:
M916_19, M916_23: M602; H807
M916_20: M307; H807
M916_21: M401; H807
M916_22: M302; H807

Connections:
!M-STOP: M916_20.L1; also elsewhere on the board
!SP_DY: M916_20.F2; also elsewhere on the board
!ST_CK_0P: M916_23.L2; also elsewhere on the board
!TM_EN: M916_21.J2, M916_21.K2; also elsewhere on the board
!TS03: M916_23.H2, M916_23.J2, M916_23.K2; also elsewhere on the board
!U+M_DY: M916_20.E2, M916_20.N1; also elsewhere on the board
!XSAD: M916_19.L2; also elsewhere on the board
!XSTA: M916_19.H2, M916_19.J2, M916_19.K2, M916_20.K2, M916_20.L2, M916_22.M2, M916_22.N2; also elsewhere on the board
+3V@D10U1: M916_20.M1; also elsewhere on the board
CSTA: M916_22.P2; also elsewhere on the board
GND: M916_19.C2, M916_19.T1, M916_20.C2, M916_20.T1, M916_21.C2, M916_21.T1, M916_22.C2, M916_22.T1, M916_23.C2, M916_23.T1; also elsewhere on the board
unnamed: M916_19.R2, M916_19.S2
unnamed 391: M916_19.F2; also elsewhere on the board
unnamed 393: M916_23.F2; also elsewhere on the board
unnamed: M916_23.D2, M916_23.E2
unnamed 401: M916_21.D2; also elsewhere on the board
unnamed: M916_21.N2, M916_21.S2
unnamed 418: M916_22.T2; also elsewhere on the board
unnamed: M916_20.M2, M916_20.V2
unnamed: M916_20.P1, M916_20.V1
unnamed 450: M916_20.J2; also elsewhere on the board
unnamed: M916_20.D2, M916_20.H1
unnamed: M916_20.A1, M916_20.C1
unnamed: M916_23.R2, M916_23.S2
unnamed: M916_22.S1, M916_22.S2
unnamed: M916_22.R2, M916_22.V2
SP_DY: M916_20.H2
ST_CK: M916_23.M2, M916_23.N2, M916_23.P2; also elsewhere on the board
T_TRK: M916_20.S1, M916_20.U1; also elsewhere on the board
U+M_DY: M916_20.K1
VCC: M916_19.A2, M916_20.A2, M916_21.A2, M916_22.A2, M916_23.A2; also elsewhere on the board
XSTA: M916_19.M2, M916_19.N2, M916_19.P2; also elsewhere on the board
